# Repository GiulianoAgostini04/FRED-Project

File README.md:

# FRED-Project
Real-time concentration monitoring system based on frontal-lobe EEG signals. Features a custom PCB designed with TinkerCAD and KiCad, OpenBCI Ganglion and Arduino UNO for signal acquisition, display, and frequency-band analysis for classification. Includes circuit schematics, hardware prototyping, and a VHDL model of the decision logic.
### Title:
Design and Realisation Description of a Specialised PCB for the Study of Frontal EEG Signals Related to Mental Focus State

### Subtitle:
FRED: Focus-Related Encephalographic Device  

### Context:
Personal project developed independently

### Description:
This project involved the design of a PCB dedicated to sampling and processing EEG signals from the frontal lobe. The goal of the PCB is to monitor the user's mental state of focus, which is where the project takes its name, FRED (Focus-Related Encephalographic Device). The combination of internal components and supplemental external hardware makes it possible to correlate the system's output with the user's current focus state. Development started with a prototype built entirely on Tinkercad, which allowed to study the behaviour of each individual component and identify which ones to select for the final design. Four main stages were defined for the system: a digital stage managing the different EEG channel inputs, an analog stage handling raw signal pre-processing, a microcontroller stage built around an Arduino UNO R3 processing the output EEG signal, and an LCD stage displaying the results of the processing phase to the user. Once validated, the project moved to KiCad to produce a more stable and verified version of the prototype. The electrical schematic was organised into four sheets: digital components and input channels, analog components and pre-processing, Arduino and LCD interfacing, and the power supply scheme. This was followed by the PCB layout phase, component placement, board dimensioning, copper trace routing, and a 4-layer stack-up. The design was finally verified through ERC and DRC checks to ensure reliability. Completing the hardware side led into the software phase: describing input-channel management and LCD output control in VHDL, alongside developing the Arduino firmware to run the focus-detection algorithm.

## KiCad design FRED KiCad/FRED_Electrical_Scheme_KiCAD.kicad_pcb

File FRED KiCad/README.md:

# FRED: KiCad Section

This repository contains the KiCad design files for FRED (Focus-Related Encephalographic Device), a custom EEG acquisition board developed for an electronic engineering course project.

The board handles the full analog front-end for EEG signal acquisition (electrode input, protection, channel multiplexing, instrumentation amplification, filtering, galvanic isolation, output buffering) and a digital channel-selection block, and sends the processed signal to an Arduino for further analysis and display.

## Board overview

The design includes:

- Electrode input stage with protection and a DRL (Driven Right Leg) reference stage for common-mode rejection
- CD4052B dual multiplexer for electrode channel selection
- INA128 instrumentation amplifier
- Sallen-Key high-pass filter (fc = 1 Hz)
- Fixed-gain amplification stage (A = 10)
- 50 Hz Twin-T notch filter
- Galvanic isolation stage based on NE555 PWM modulation, a 4N35 optocoupler, and Sallen-Key demodulation
- Anti-aliasing band-pass filter and output buffer toward the Arduino ADC
- Digital block for channel selection (slide switches, 74HC74 flip-flop, 74HC04/74HC08 logic, status LEDs)

Note: intermediate export files (`.cad`, `.cmp`, `.dsn`, `.emn`, `.emp`, `.hyp`, `.wrl`) and auto-generated check reports (`DRC.rpt`, `ERC.rpt`, `report.txt`) are not versioned, since they can be regenerated at any time from the project files.

## Tools used

| Tool | Purpose |
|---|---|
| KiCad 10.0 | Schematic and PCB layout |

## How to open the project

1. Clone the repository.
2. Open `FRED_Electrical_Scheme_KiCAD.kicad_pro` with KiCad 10.0 or later.
3. Schematic and PCB print PDFs are available in the `PDF/` folder for a quick look without opening KiCad.

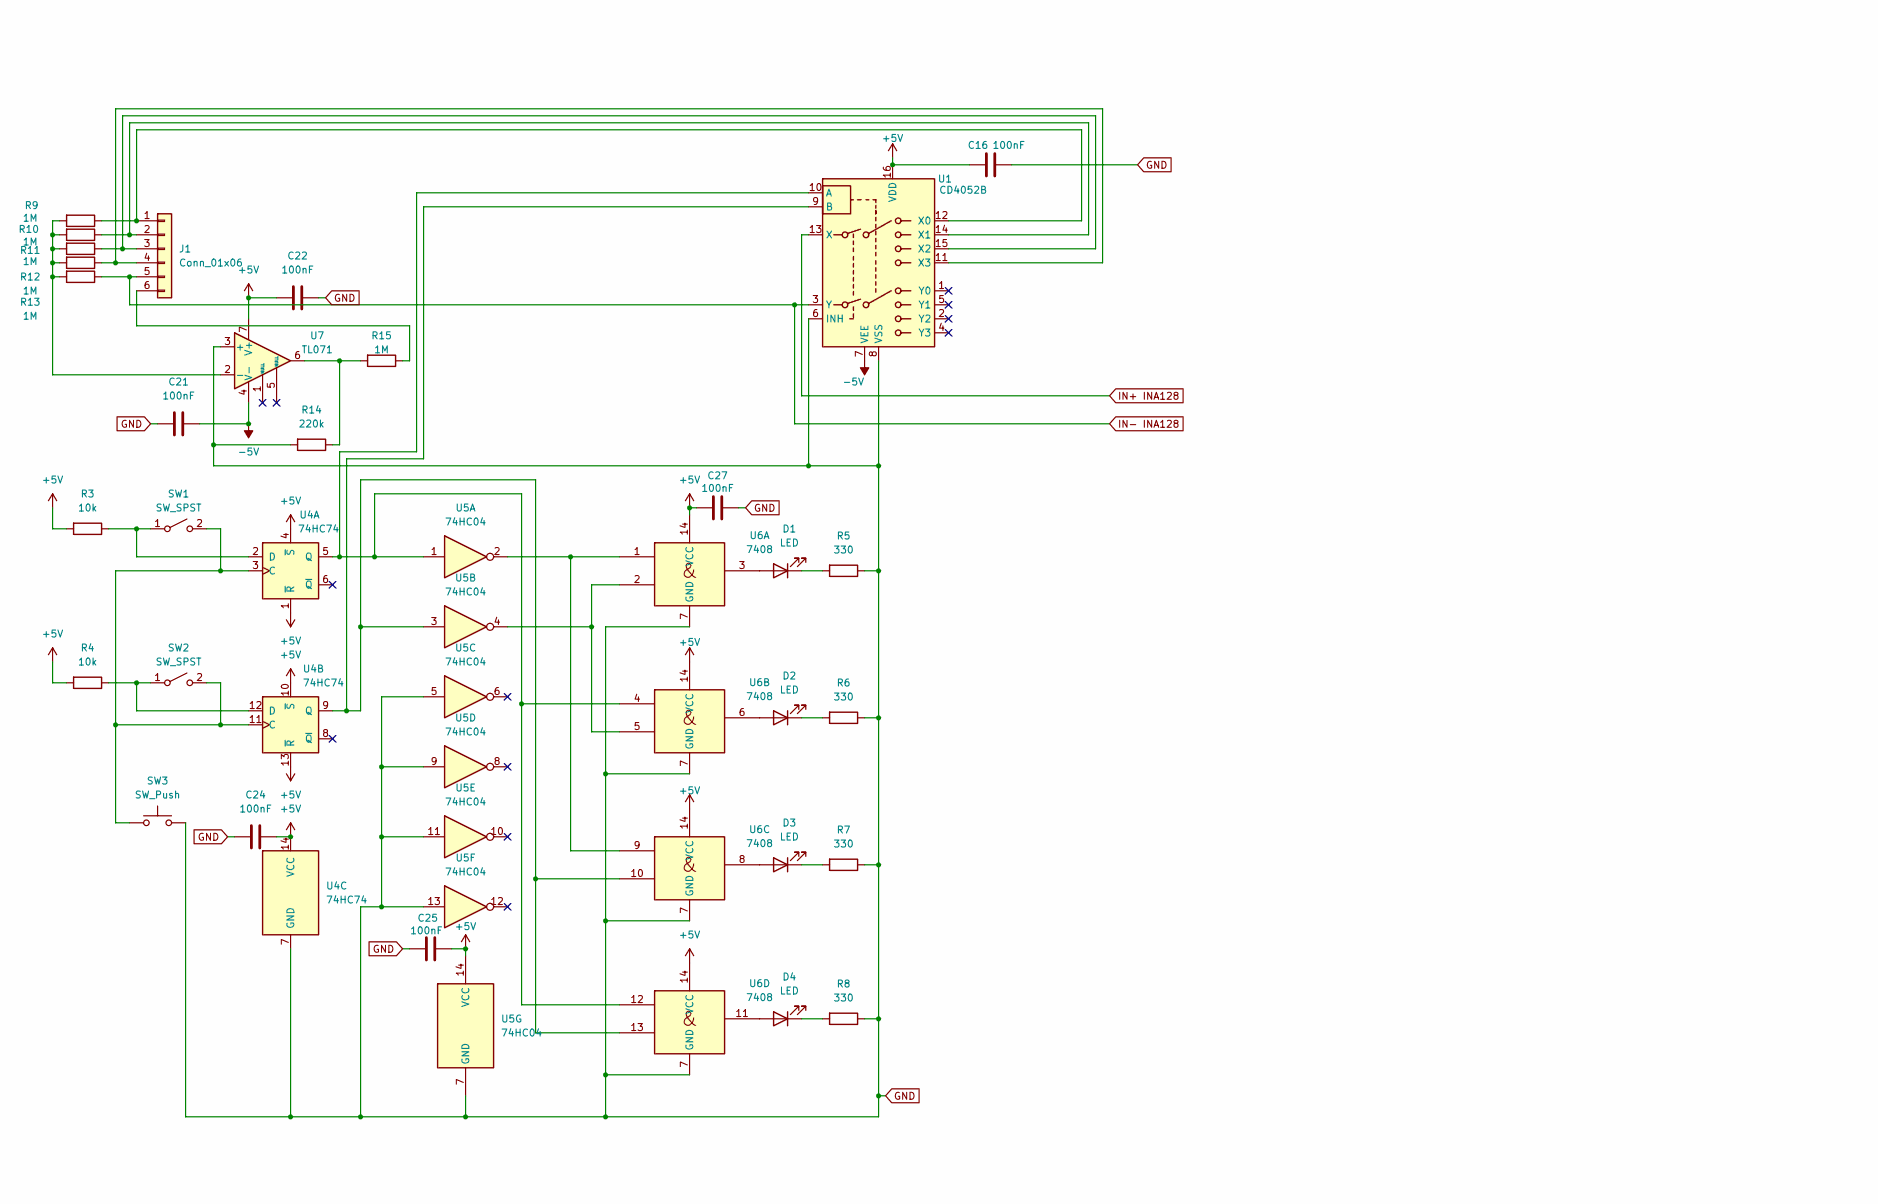
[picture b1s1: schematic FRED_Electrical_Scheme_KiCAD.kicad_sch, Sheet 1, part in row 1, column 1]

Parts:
C16, C21, C22, C24, C25, C27: 100nF; C_Disc_D5.0mm_W2.5mm_P2.50mm
D1, D2, D3, D4: LED; D_DO-35_SOD27_P7.62mm_Horizontal
J1: Conn_01x06; PinHeader_1x06_P2.54mm_Vertical
R3, R4: 10k; R_Axial_DIN0207_L6.3mm_D2.5mm_P10.16mm_Horizontal
R5, R6, R7, R8: 330; R_Axial_DIN0207_L6.3mm_D2.5mm_P10.16mm_Horizontal
R9, R10, R11, R12, R13, R15: 1M; R_Axial_DIN0207_L6.3mm_D2.5mm_P10.16mm_Horizontal
R14: 220k; R_Axial_DIN0207_L6.3mm_D2.5mm_P10.16mm_Horizontal
SW1, SW2: SW_SPST; SW_DIP_SPSTx01_Slide_9.78x4.72mm_W7.62mm_P2.54mm
SW3: SW_Push; SW_PUSH_6mm
U1: CD4052B; DIP-16_W7.62mm
U4: 74HC74; DIP-14_W7.62mm
U5: 74HC04; DIP-14_W7.62mm
U6: 7408; DIP-14_W7.62mm
U7: TL071; DIP-8-16_W7.62mm

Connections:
+5V: C16.2, C22.2, C24.1, C25.1, C27.2, R3.2, R4.2, U1.16 (VDD), U4.1 (~R), U4.4 (~S), U4.10 (~S), U4.13 (~R), U4.14 (VCC), U5.14 (VCC), U6.14 (VCC), U7.7 (V+); also elsewhere on the board
-5V: C21.1, U1.7 (VEE), U7.4 (V-); also elsewhere on the board
GND: C16.1, C21.2, C22.1, C24.2, C25.2, C27.1, R5.1, R6.1, R7.1, R8.1, R14.2, SW3.2, U1.6 (INH), U1.8 (VSS), U4.7 (GND), U5.5, U5.7 (GND), U5.9, U5.11, U5.13, U6.7 (GND), U7.3 (+); also elsewhere on the board
IN+ INA128: U1.13 (X); also elsewhere on the board
IN- INA128: J1.5, R13.1, U1.3 (Y); also elsewhere on the board
unnamed: D1.2 (A), U6.3
unnamed: D1.1 (K), R5.2
unnamed: D2.2 (A), U6.6
unnamed: D2.1 (K), R6.2
unnamed: D3.2 (A), U6.8
unnamed: D3.1 (K), R7.2
unnamed: D4.2 (A), U6.11
unnamed: D4.1 (K), R8.2
unnamed: J1.1, R9.1, U1.12 (X0)
unnamed: J1.2, R10.1, U1.14 (X1)
unnamed: J1.3, R11.1, U1.15 (X2)
unnamed: J1.4, R12.1, U1.11 (X3)
unnamed: J1.6, R15.1
unnamed: R14.1, R15.2, U7.6
unnamed: R3.1, SW1.1 (A), U4.2 (D)
unnamed: SW1.2 (B), SW2.2 (B), SW3.1, U4.3 (C), U4.11 (C)
unnamed: R4.1, SW2.1 (A), U4.12 (D)
unnamed: U1.10 (A), U4.5 (Q), U5.1, U6.4, U6.12
unnamed: U1.9 (B), U4.9 (Q), U5.3, U6.10, U6.13
unnamed: U5.2, U6.1, U6.9
unnamed: U5.4, U6.2, U6.5
unnamed: R9.2, R10.2, R11.2, R12.2, R13.2, U7.2 (-)

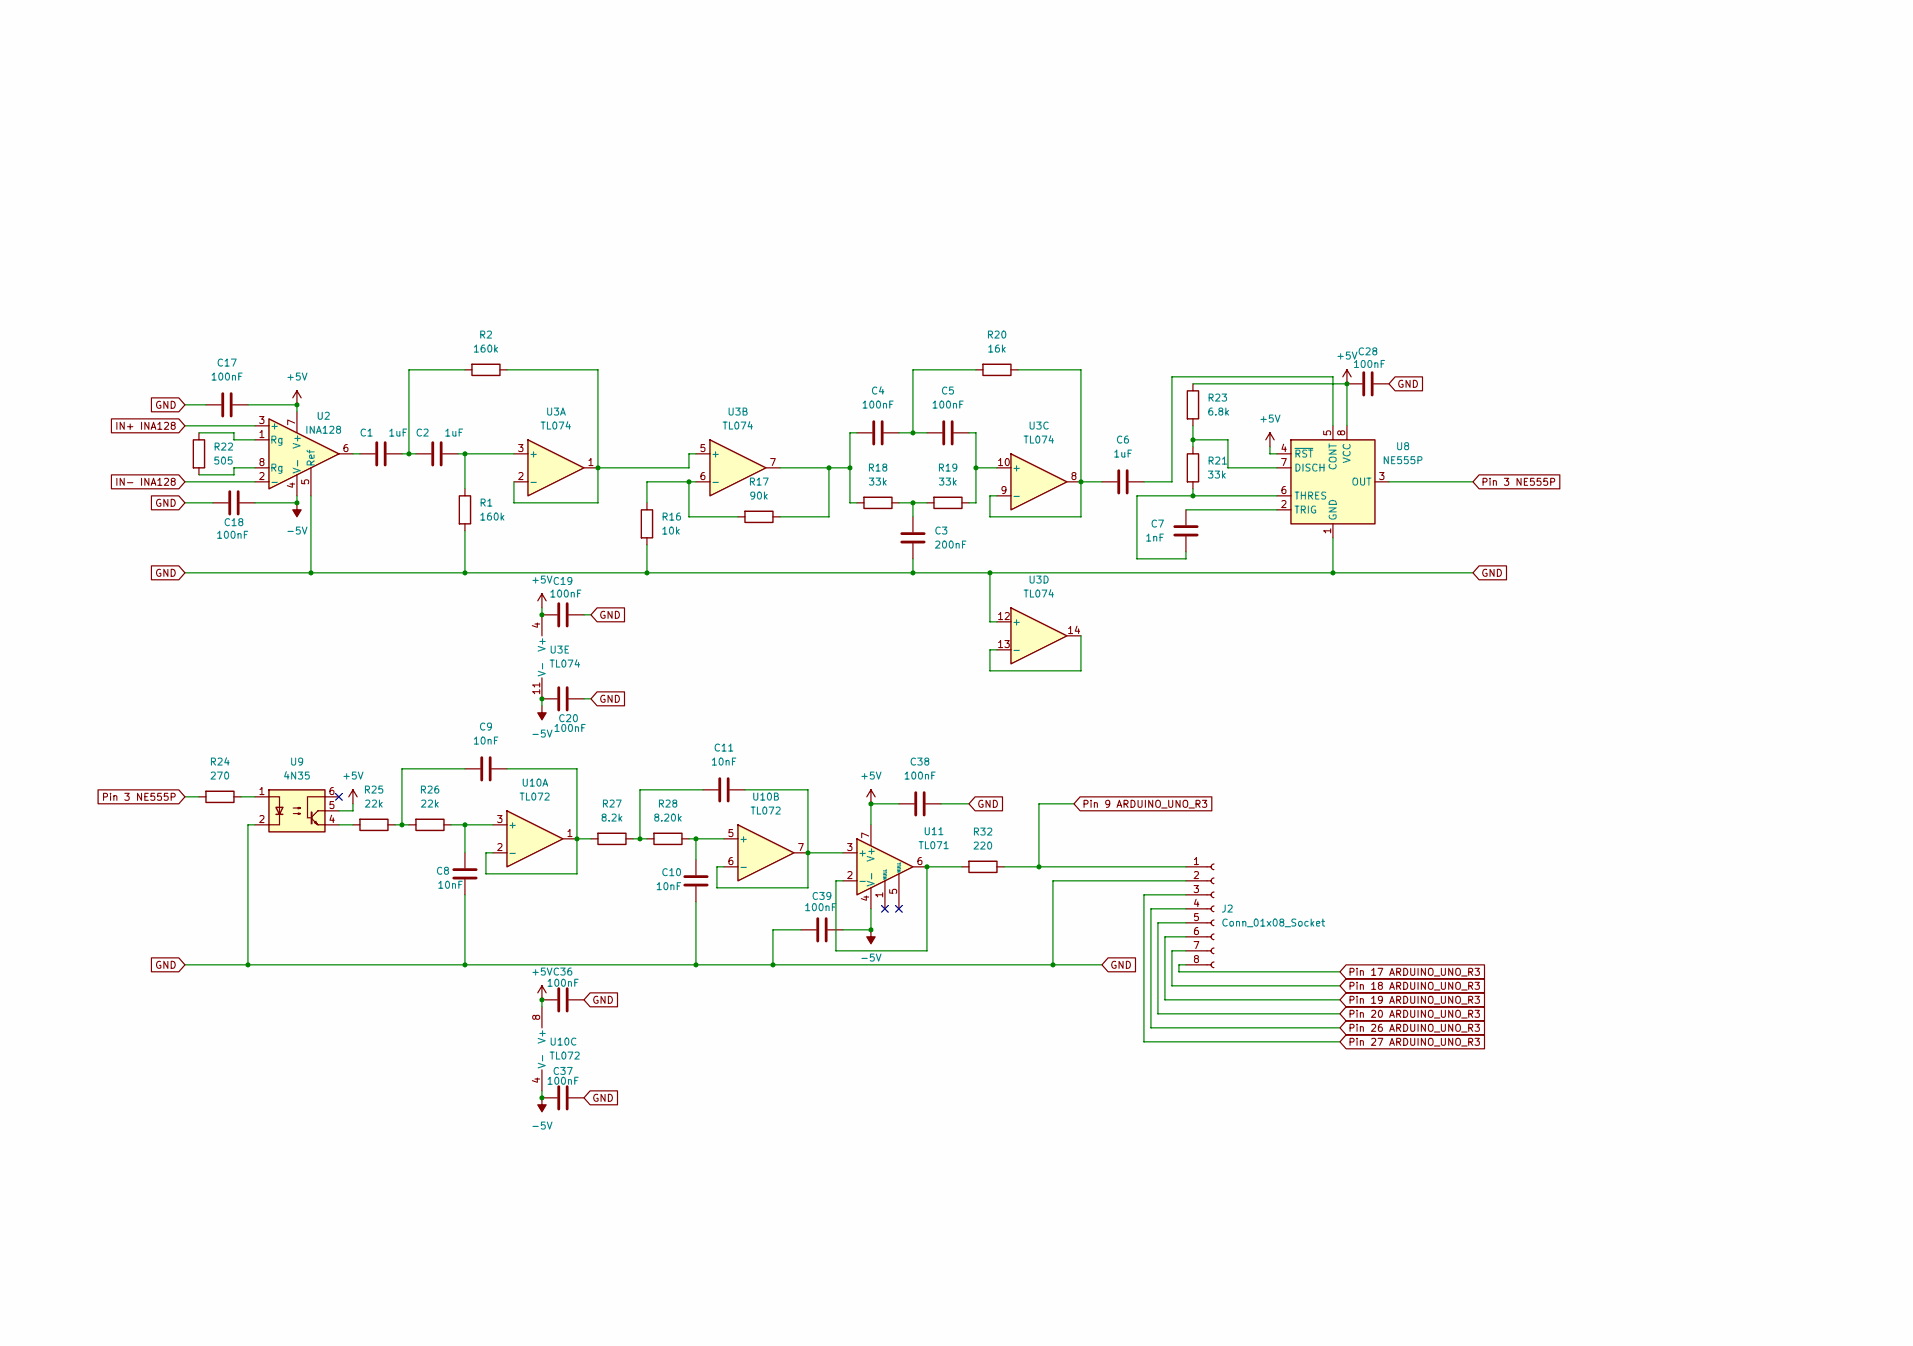
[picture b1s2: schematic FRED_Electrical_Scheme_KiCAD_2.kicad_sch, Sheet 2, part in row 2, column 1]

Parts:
C1, C2, C6: 1uF; C_0603_1608Metric
C3: 200nF; C_Disc_D5.0mm_W2.5mm_P5.00mm
C4, C5: 100nF; C_Disc_D5.0mm_W2.5mm_P5.00mm
C7: 1nF; C_Disc_D5.0mm_W2.5mm_P5.00mm
C8, C9, C10, C11: 10nF; C_Disc_D5.0mm_W2.5mm_P5.00mm
C17, C18, C19, C20, C28, C36, C37, C38, C39: 100nF; C_Disc_D5.0mm_W2.5mm_P2.50mm
J2: Conn_01x08_Socket; PinSocket_1x08_P2.54mm_Vertical
R1, R2: 160k; R_Axial_DIN0207_L6.3mm_D2.5mm_P10.16mm_Horizontal
R16: 10k; R_Axial_DIN0207_L6.3mm_D2.5mm_P10.16mm_Horizontal
R17: 90k; R_Axial_DIN0207_L6.3mm_D2.5mm_P10.16mm_Horizontal
R18, R19, R21: 33k; R_Axial_DIN0207_L6.3mm_D2.5mm_P10.16mm_Horizontal
R20: 16k; R_Axial_DIN0207_L6.3mm_D2.5mm_P10.16mm_Horizontal
R22: 505; R_Axial_DIN0207_L6.3mm_D2.5mm_P10.16mm_Horizontal
R23: 6.8k; R_Axial_DIN0207_L6.3mm_D2.5mm_P10.16mm_Horizontal
R24: 270; R_Axial_DIN0207_L6.3mm_D2.5mm_P10.16mm_Horizontal
R25, R26: 22k; R_Axial_DIN0207_L6.3mm_D2.5mm_P10.16mm_Horizontal
R27: 8.2k; R_Axial_DIN0207_L6.3mm_D2.5mm_P10.16mm_Horizontal
R28: 8.20k; R_Axial_DIN0207_L6.3mm_D2.5mm_P10.16mm_Horizontal
R32: 220; R_Axial_DIN0207_L6.3mm_D2.5mm_P10.16mm_Horizontal
U2: INA128; DIP-8-16_W7.62mm
U3: TL074; DIP-14_W7.62mm
U8: NE555P; DIP-8_W7.62mm
U9: 4N35; DIP-6_W7.62mm
U10: TL072; DIP-8-16_W7.62mm
U11: TL071; DIP-8-16_W7.62mm

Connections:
+5V: C17.1, C19.1, C28.2, C36.2, C38.2, R23.1, U2.7 (V+), U3.4 (V+), U8.4 (~RST), U8.8 (VCC), U9.5, U10.8 (V+), U11.7 (V+); also elsewhere on the board
-5V: C18.1, C20.2, C37.2, C39.1, U2.4 (V-), U3.11 (V-), U10.4 (V-), U11.4 (V-); also elsewhere on the board
GND: C3.2, C8.2, C10.2, C17.2, C18.2, C19.2, C20.1, C28.1, C36.1, C37.1, C38.1, C39.2, J2.2, R1.2, R16.2, U2.5 (Ref), U3.12 (+), U8.1 (GND), U9.2; also elsewhere on the board
IN+ INA128: U2.3 (+); also elsewhere on the board
IN- INA128: U2.2 (-); also elsewhere on the board
unnamed: C1.1, U2.6
unnamed: C1.2, C2.1, R2.2
unnamed: C3.1, R18.1, R19.2
unnamed: C4.1, C5.2, R20.2
unnamed: C4.2, R17.1, R18.2, U3.7
unnamed: C9.2, R25.1, R26.2
unnamed: C11.2, R27.1, R28.2
unnamed: R22.1, U2.1 (Rg)
unnamed: R22.2, U2.8 (Rg)
unnamed: R24.1, U9.1
unnamed: R25.2, U9.4
unnamed: C2.2, R1.1, U3.3 (+)
unnamed: R2.1, U3.1, U3.2 (-), U3.5 (+)
unnamed: R16.1, R17.2, U3.6 (-)
unnamed: C5.1, R19.1, U3.10 (+)
unnamed: C6.2, R20.1, U3.8, U3.9 (-)
unnamed: U3.13 (-), U3.14
unnamed: C6.1, U8.5 (CONT)
unnamed: R21.1, R23.2, U8.7 (DISCH)
unnamed: C7.1, R21.2, U8.6 (THRES)
unnamed: C7.2, U8.2 (TRIG)
unnamed: C8.1, R26.1, U10.3 (+)
unnamed: C9.1, R27.2, U10.1, U10.2 (-)
unnamed: C10.1, R28.1, U10.5 (+)
unnamed: C11.1, U10.6 (-), U10.7, U11.3 (+)
unnamed: R32.2, U11.2 (-), U11.6
Pin 3 NE555P: R24.2, U8.3 (OUT)
Pin 9 ARDUINO_UNO_R3: J2.1, R32.1; also elsewhere on the board
Pin 17 ARDUINO_UNO_R3: J2.8; also elsewhere on the board
Pin 18 ARDUINO_UNO_R3: J2.7; also elsewhere on the board
Pin 19 ARDUINO_UNO_R3: J2.6; also elsewhere on the board
Pin 20 ARDUINO_UNO_R3: J2.5; also elsewhere on the board
Pin 26 ARDUINO_UNO_R3: J2.4; also elsewhere on the board
Pin 27 ARDUINO_UNO_R3: J2.3; also elsewhere on the board

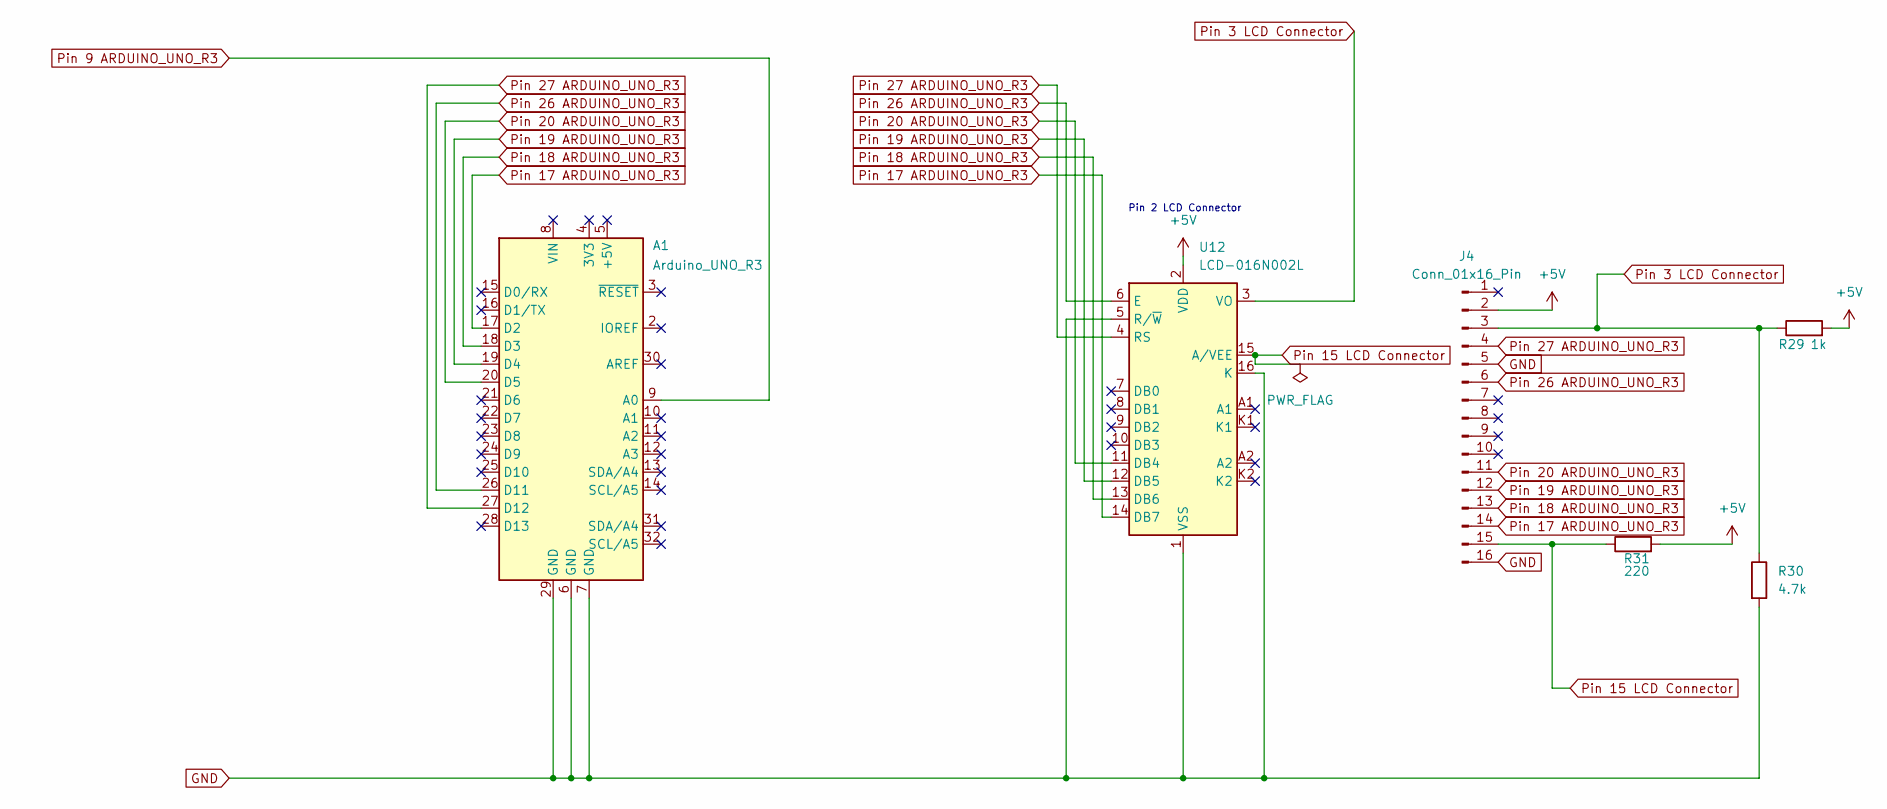
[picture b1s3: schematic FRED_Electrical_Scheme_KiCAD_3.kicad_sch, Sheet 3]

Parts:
A1: Arduino_UNO_R3
J4: Conn_01x16_Pin; PinSocket_1x16_P2.54mm_Vertical
R29: 1k; R_Axial_DIN0207_L6.3mm_D2.5mm_P10.16mm_Horizontal
R30: 4.7k; R_Axial_DIN0207_L6.3mm_D2.5mm_P10.16mm_Horizontal
R31: 220; R_Axial_DIN0207_L6.3mm_D2.5mm_P10.16mm_Horizontal
U12: LCD-016N002L

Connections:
+5V: J4.2, R29.2, R31.2, U12.2 (VDD); also elsewhere on the board
GND: A1.6 (GND), A1.7 (GND), A1.29 (GND), J4.5, J4.16, R30.2, U12.1 (VSS), U12.5 (R/~W), U12.16 (K); also elsewhere on the board
Pin 3 LCD Connector: J4.3, R29.1, R30.1, U12.3 (VO)
Pin 9 ARDUINO_UNO_R3: A1.9 (A0); also elsewhere on the board
Pin 15 LCD Connector: J4.15, R31.1, U12.15 (A/VEE)
Pin 17 ARDUINO_UNO_R3: A1.17 (D2), J4.14, U12.14 (DB7); also elsewhere on the board
Pin 18 ARDUINO_UNO_R3: A1.18 (D3), J4.13, U12.13 (DB6); also elsewhere on the board
Pin 19 ARDUINO_UNO_R3: A1.19 (D4), J4.12, U12.12 (DB5); also elsewhere on the board
Pin 20 ARDUINO_UNO_R3: A1.20 (D5), J4.11, U12.11 (DB4); also elsewhere on the board
Pin 26 ARDUINO_UNO_R3: A1.26 (D11), J4.6, U12.6 (E); also elsewhere on the board
Pin 27 ARDUINO_UNO_R3: A1.27 (D12), J4.4, U12.4 (RS); also elsewhere on the board

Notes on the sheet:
Pin 2 LCD Connector

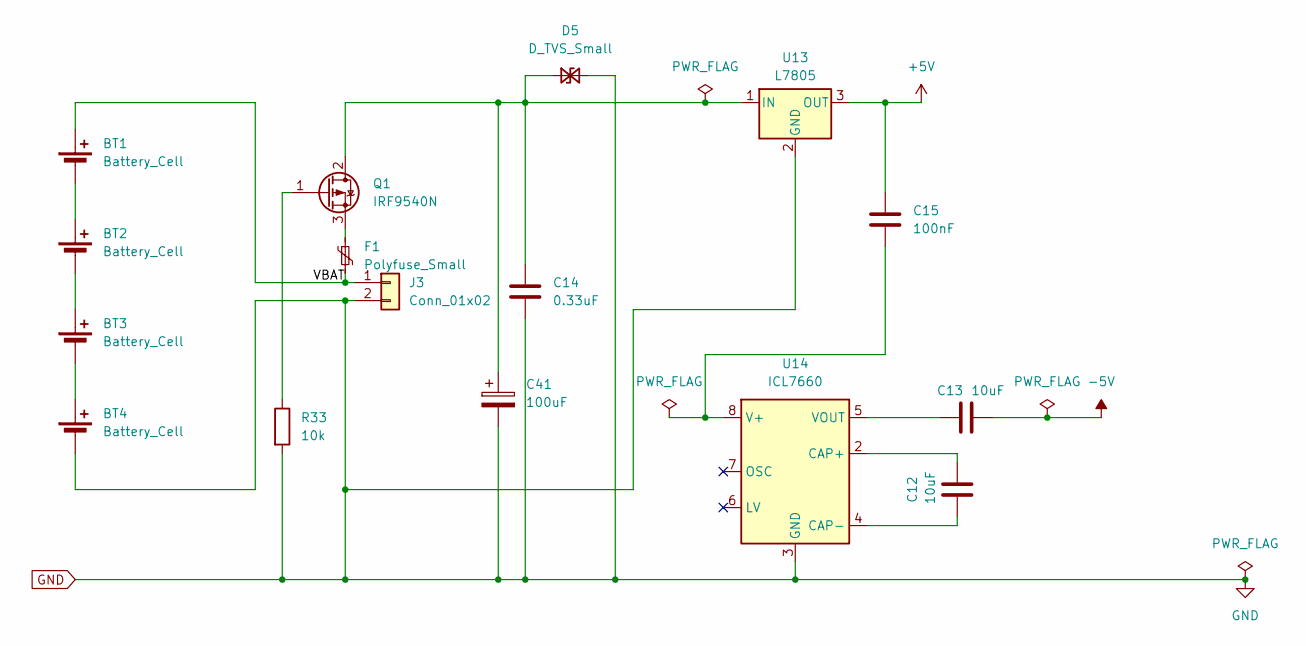
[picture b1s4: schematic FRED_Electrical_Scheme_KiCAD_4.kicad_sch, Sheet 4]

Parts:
BT1, BT2, BT3, BT4: Battery_Cell
C12, C13: 10uF; C_0603_1608Metric
C14: 0.33uF; C_Disc_D5.0mm_W2.5mm_P5.00mm
C15: 100nF; C_Disc_D5.0mm_W2.5mm_P5.00mm
C41: 100uF; CP_Radial_D8.0mm_P3.50mm
D5: D_TVS_Small; D_A-405_P7.62mm_Horizontal
F1: Polyfuse_Small; Fuse_Bourns_MF-RHT050
J3: Conn_01x02; TerminalBlock_Phoenix_MKDS-1,5-2-5.08_1x02_P5.08mm_Horizont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
Q1: IRF9540N; TO-220-3_Vertical
R33: 10k; R_Axial_DIN0207_L6.3mm_D2.5mm_P10.16mm_Horizontal
U13: L7805; TO-220-3_Vertical
U14: ICL7660; CERDIP-8_W7.62mm_SideBrazed

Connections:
+5V: C15.1, U13.3 (OUT); also elsewhere on the board
-5V: C13.1; also elsewhere on the board
/Sheet 2/Sheet 4/VBAT: BT1.1 (+), F1.2, J3.1
GND: BT4.2 (-), C14.2, C41.2, D5.2 (A2), J3.2, R33.2, U13.2 (GND), U14.3 (GND); also elsewhere on the board
unnamed: BT1.2 (-), BT2.1 (+)
unnamed: BT2.2 (-), BT3.1 (+)
unnamed: BT3.2 (-), BT4.1 (+)
unnamed: C14.1, C41.1, D5.1 (A1), Q1.2 (D), U13.1 (IN)
unnamed: Q1.1 (G), R33.1
unnamed: F1.1, Q1.3 (S)
unnamed: C12.1, U14.2 (CAP+)
unnamed: C12.2, U14.4 (CAP-)
unnamed: C15.2, U14.8 (V+)
unnamed: C13.2, U14.5 (VOUT)

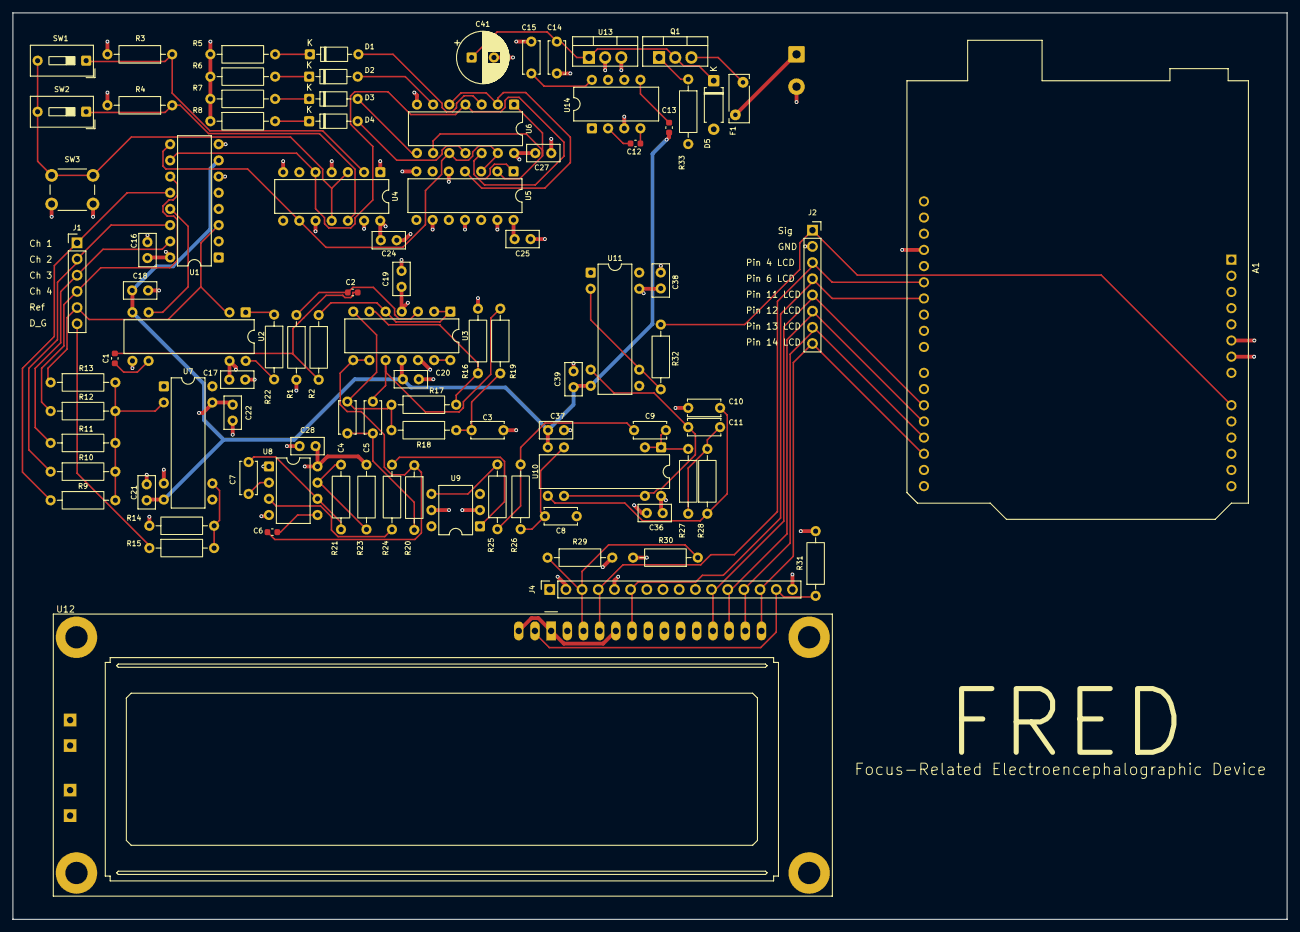
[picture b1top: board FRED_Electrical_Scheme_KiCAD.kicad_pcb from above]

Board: 4 copper layers, 200.0 x 142.3 mm, 93 parts (1 on the bottom side), 71 nets.
